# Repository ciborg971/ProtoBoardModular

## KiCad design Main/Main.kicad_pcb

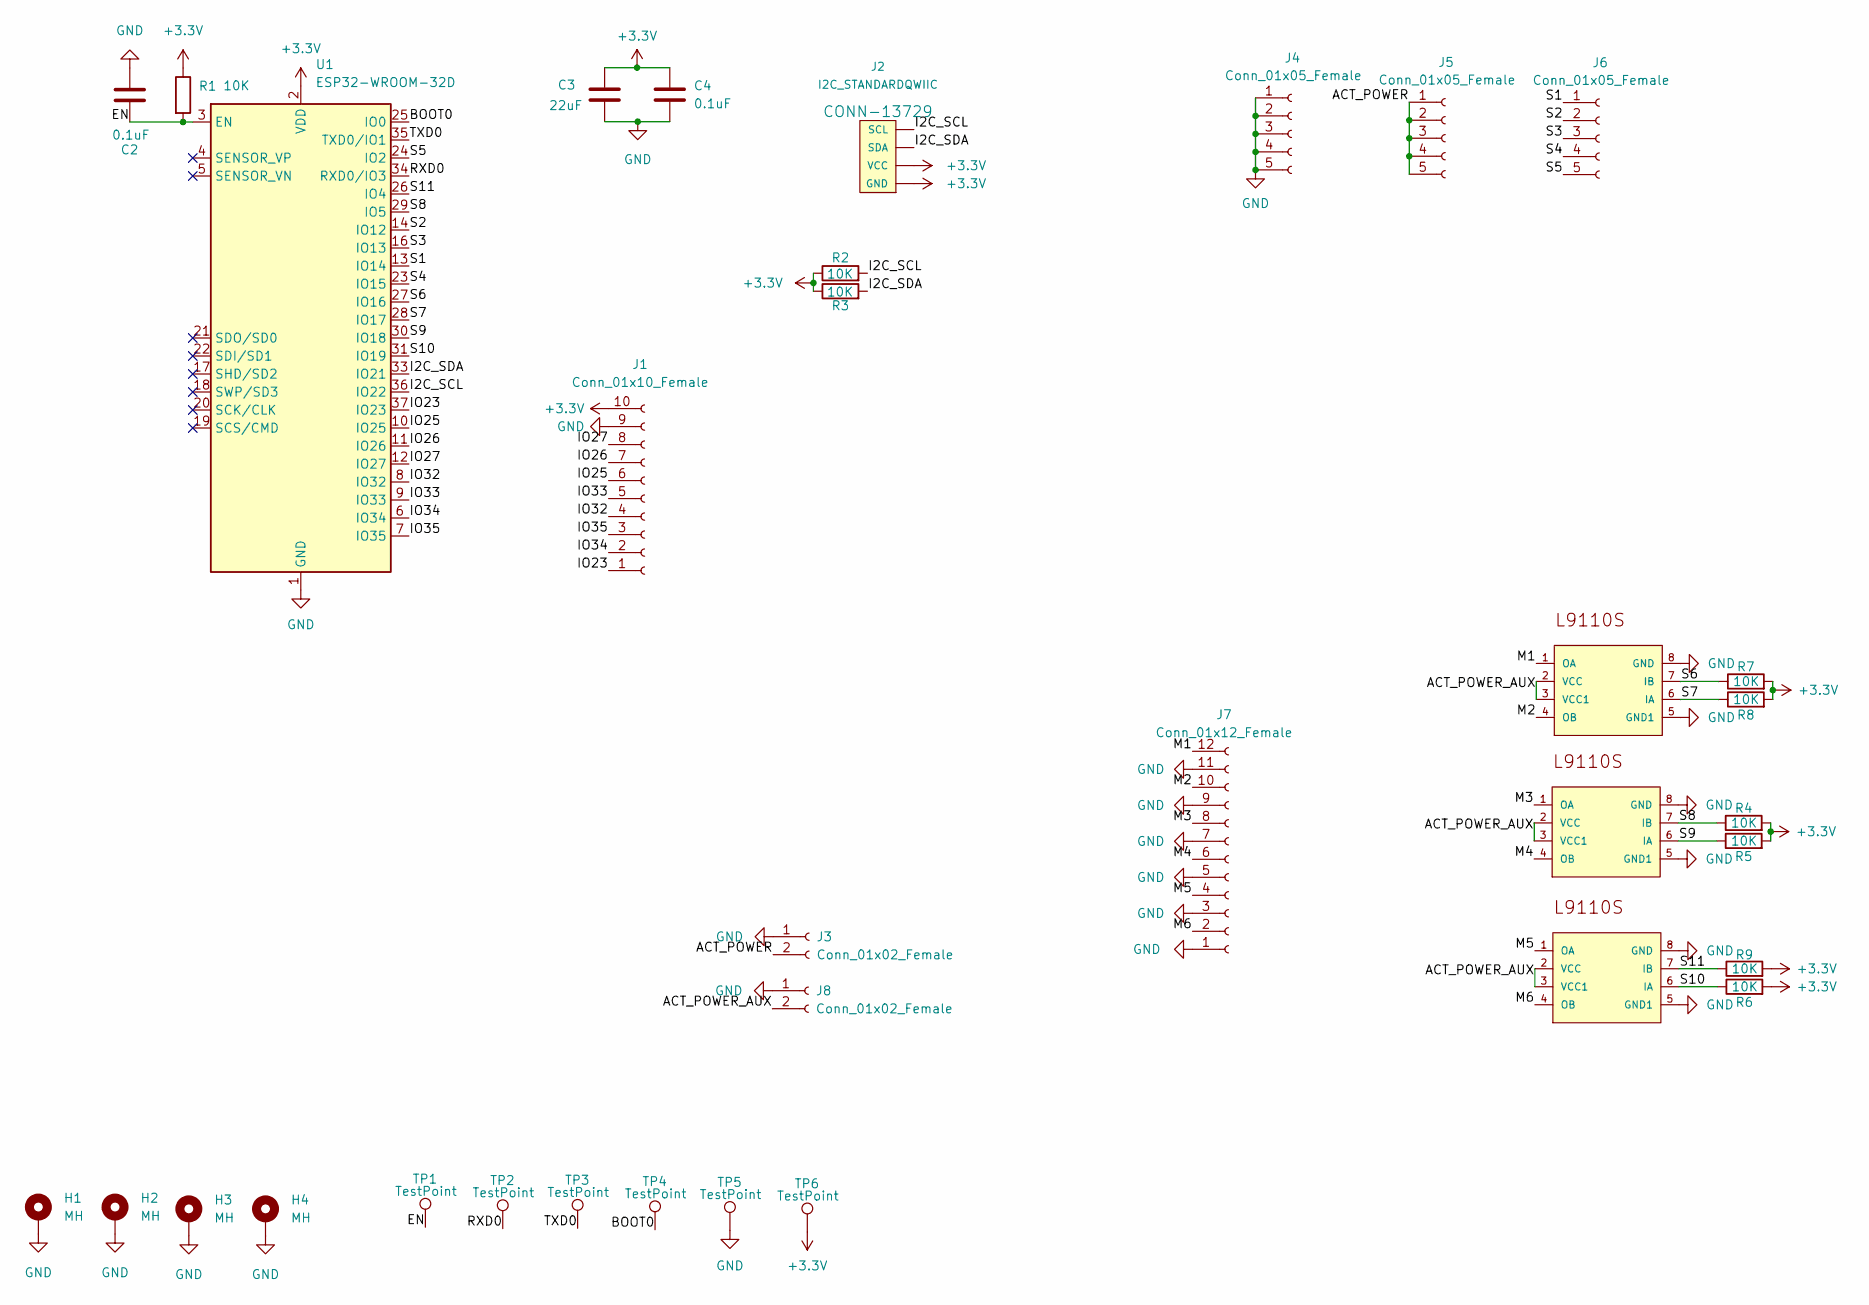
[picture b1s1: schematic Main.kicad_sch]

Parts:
C2, C4: 0.1uF; C_0402_1005Metric; LCSC C178771
C3: 22uF; C_0402_1005Metric; LCSC C2836678
H1, H2, H3, H4: MH; MountingHole_2.2mm_M2_Pad
IC1, IC2, IC3: L9110S; SOIC127P600X150-8; LCSC C2984833
J1: Conn_01x10_Female; Hirose_DF13-10P-1.25DSA_1x10_P1.25mm_Vertical
J2: I2C_STANDARDQWIIC; 1X04_1MM_RA
J3, J8: Conn_01x02_Female; PinSocket_1x02_P2.54mm_Vertical
J4, J5, J6: Conn_01x05_Female; PinHeader_1x05_P2.54mm_Vertical
J7: Conn_01x12_Female; Hirose_DF13-12P-1.25DSA_1x12_P1.25mm_Vertical
R1, R2, R3, R4, R5, R6, R7, R8, R9: 10K; R_0402_1005Metric; LCSC C325396
TP1, TP2, TP3, TP4, TP5, TP6: TestPoint; TestPoint_Pad_1.5x1.5mm
U1: ESP32-WROOM-32D; ESP32-WROOM-32; LCSC C473012

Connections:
+3V3: C3.1, C4.1, J1.10, J2.1 (GND), J2.2 (VCC), R1.1, R2.1, R3.1, R4.2, R5.2, R6.2, R7.2, R8.2, R9.2, TP6.1, U1.2 (VDD)
/ACT_POWER: J3.2, J5.1, J5.2, J5.3, J5.4, J5.5
/ACT_POWER_AUX: IC1.2 (VCC), IC1.3 (VCC1), IC2.2 (VCC), IC2.3 (VCC1), IC3.2 (VCC), IC3.3 (VCC1), J8.2
/BOOT0: TP4.1, U1.25 (IO0)
/EN: C2.2, R1.2, TP1.1, U1.3 (EN)
/I2C_SCL: J2.4 (SCL), R2.2, U1.36 (IO22)
/I2C_SDA: J2.3 (SDA), R3.2, U1.33 (IO21)
/IO23: J1.1, U1.37 (IO23)
/IO25: J1.6, U1.10 (IO25)
/IO26: J1.7, U1.11 (IO26)
/IO27: J1.8, U1.12 (IO27)
/IO32: J1.4, U1.8 (IO32)
/IO33: J1.5, U1.9 (IO33)
/IO34: J1.2, U1.6 (IO34)
/IO35: J1.3, U1.7 (IO35)
/M1: IC3.1 (OA), J7.12
/M2: IC3.4 (OB), J7.10
/M3: IC1.1 (OA), J7.8
/M4: IC1.4 (OB), J7.6
/M5: IC2.1 (OA), J7.4
/M6: IC2.4 (OB), J7.2
/RXD0: TP2.1, U1.34 (RXD0/IO3)
/S1: J6.1, U1.13 (IO14)
/S2: J6.2, U1.14 (IO12)
/S3: J6.3, U1.16 (IO13)
/S4: J6.4, U1.23 (IO15)
/S5: J6.5, U1.24 (IO2)
/S6: IC3.7 (IB), R7.1, U1.27 (IO16)
/S7: IC3.6 (IA), R8.1, U1.28 (IO17)
/S8: IC1.7 (IB), R4.1, U1.29 (IO5)
/S9: IC1.6 (IA), R5.1, U1.30 (IO18)
/S10: IC2.6 (IA), R6.1, U1.31 (IO19)
/S11: IC2.7 (IB), R9.1, U1.26 (IO4)
/TXD0: TP3.1, U1.35 (TXD0/IO1)
GND: C2.1, C3.2, C4.2, H1.1, H2.1, H3.1, H4.1, IC1.5 (GND1), IC1.8 (GND), IC2.5 (GND1), IC2.8 (GND), IC3.5 (GND1), IC3.8 (GND), J1.9, J3.1, J4.1, J4.2, J4.3, J4.4, J4.5, J7.1, J7.3, J7.5, J7.7, J7.9, J7.11, J8.1, TP5.1, U1.1 (GND), U1.15 (GND), U1.38 (GND), U1.39 (GND)

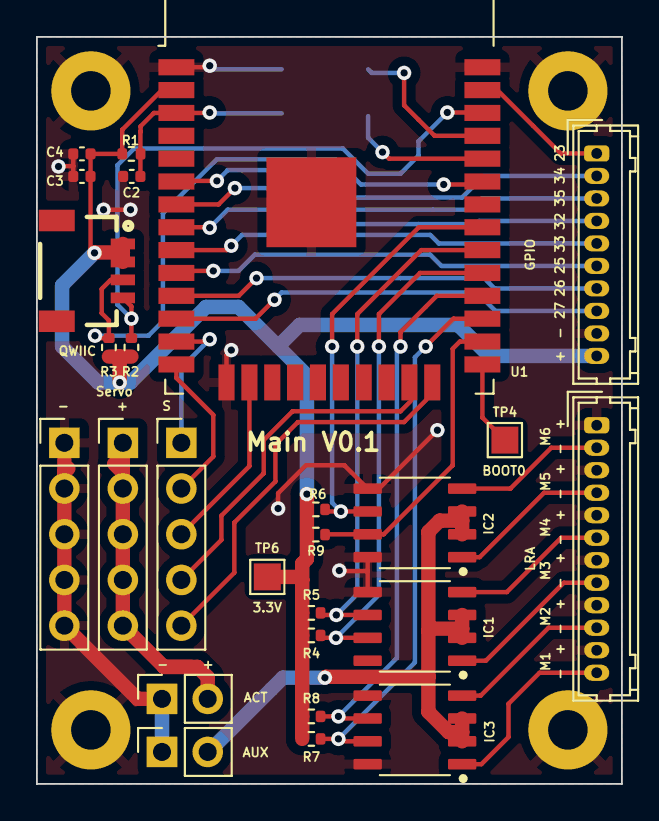
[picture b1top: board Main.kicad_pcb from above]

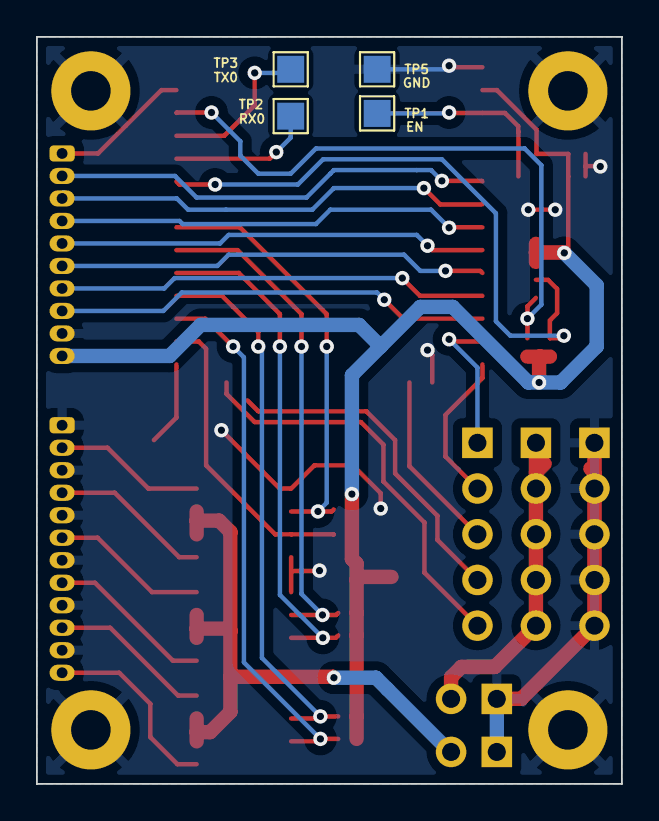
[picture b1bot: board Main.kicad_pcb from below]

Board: 2 copper layers, 32.5 x 41.5 mm, 34 parts (4 on the bottom side), 35 nets.

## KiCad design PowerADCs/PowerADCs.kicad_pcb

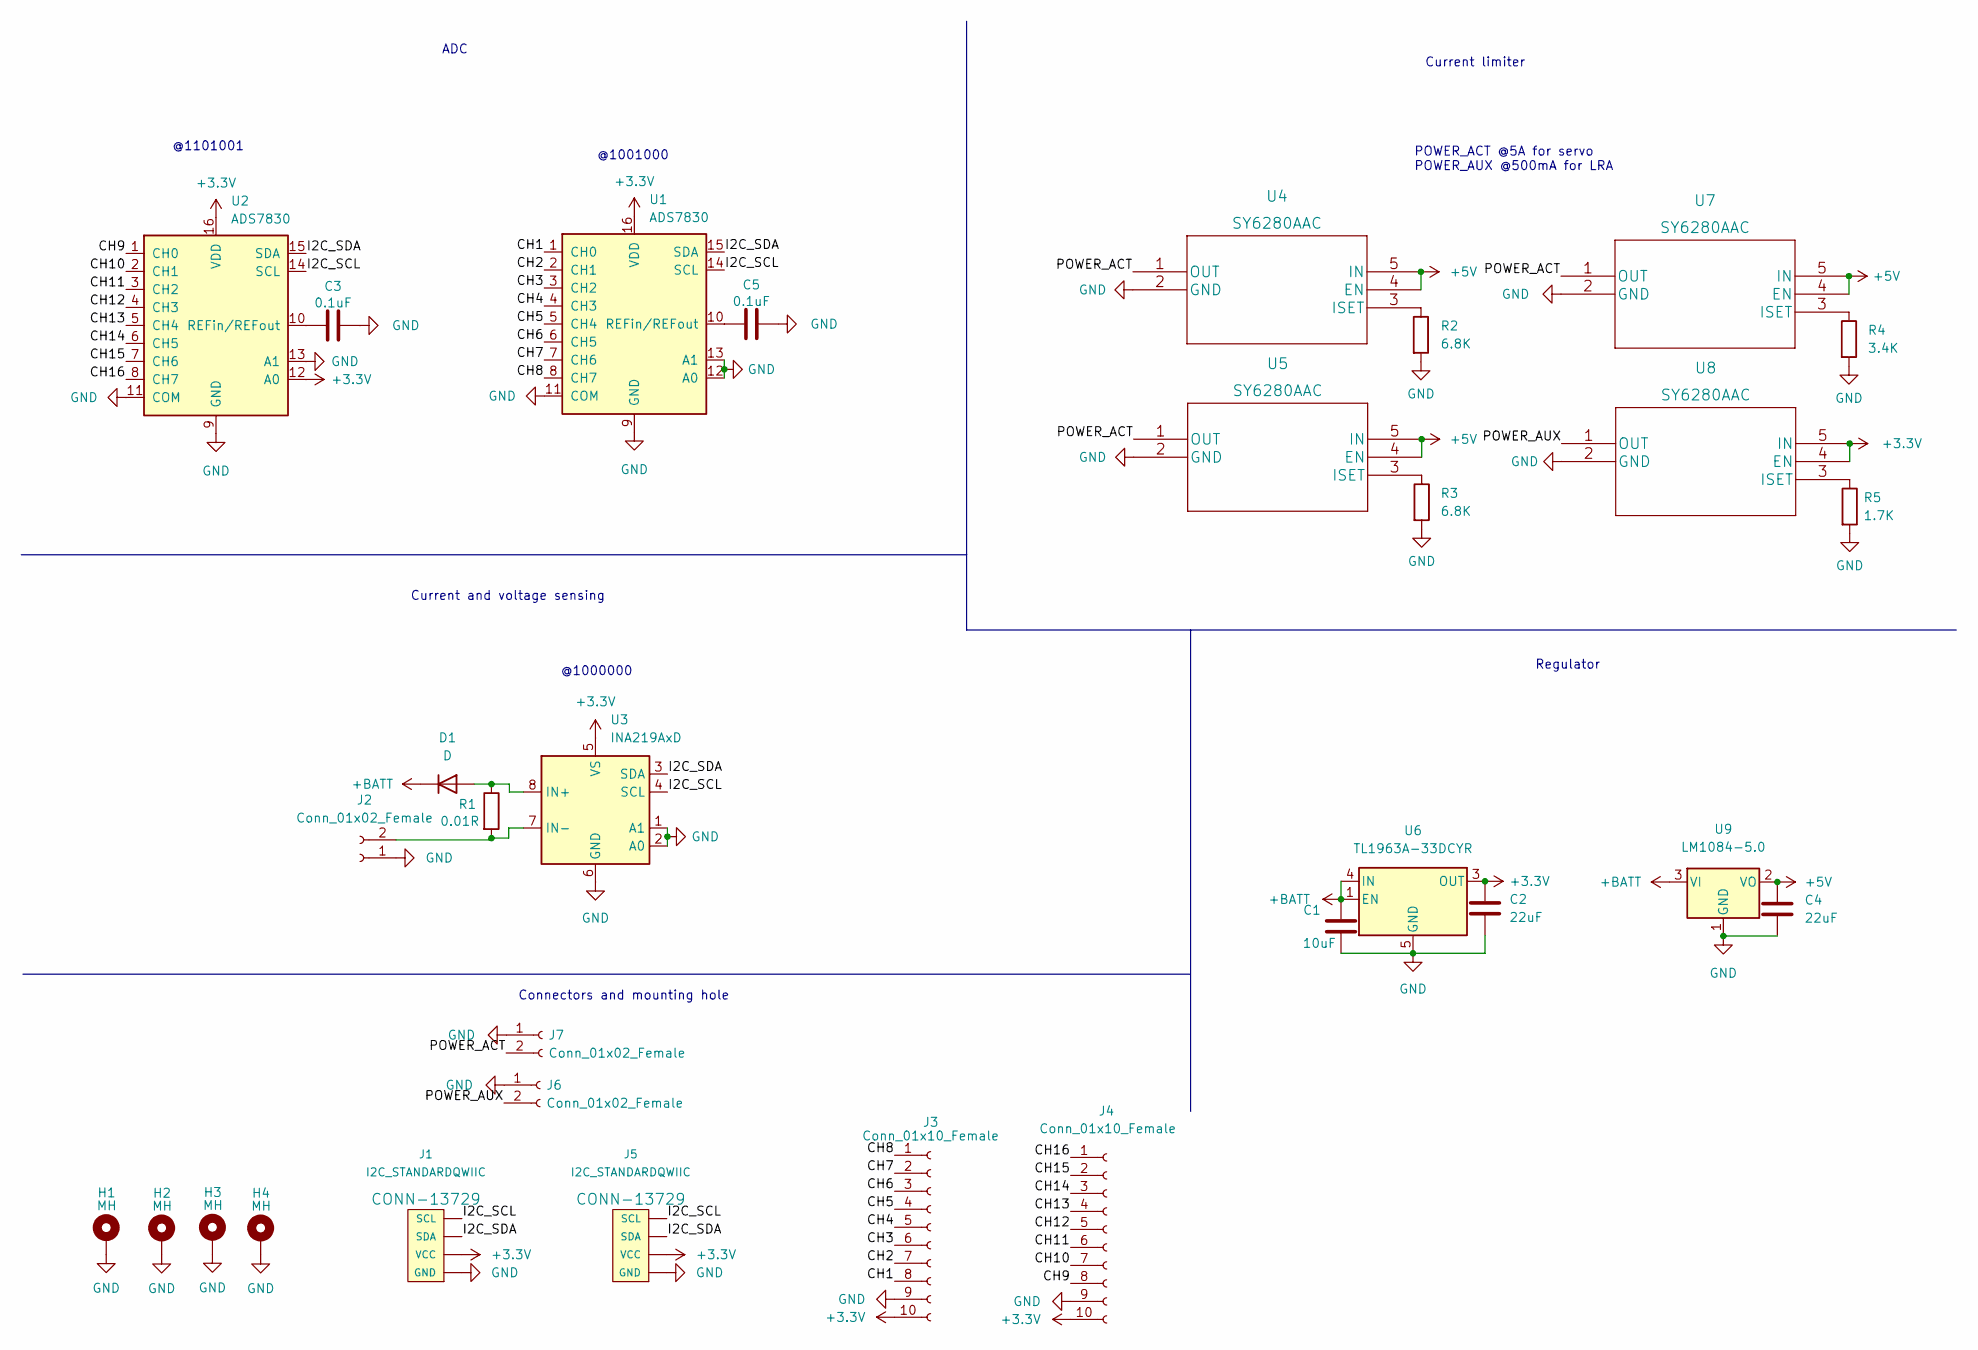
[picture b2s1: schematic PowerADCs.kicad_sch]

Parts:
C1: 10uF; C_0402_1005Metric
C2, C4: 22uF; C_0402_1005Metric
C3, C5: 0.1uF; C_0402_1005Metric
D1: D; D_0402_1005Metric
H1, H2, H3, H4: MH; MountingHole_2.2mm_M2_Pad
J1, J5: I2C_STANDARDQWIIC; 1X04_1MM_RA
J2, J6, J7: Conn_01x02_Female; PinSocket_1x02_P2.54mm_Vertical
J3, J4: Conn_01x10_Female; Hirose_DF13-10P-1.25DSA_1x10_P1.25mm_Vertical
R1: 0.01R; R_0402_1005Metric
R2, R3: 6.8K; R_0402_1005Metric
R4: 3.4K; R_0402_1005Metric
R5: 1.7K; R_0402_1005Metric
U1, U2: ADS7830; TSSOP-16_4.4x5mm_P0.65mm
U3: INA219AxD; SOIC-8_3.9x4.9mm_P1.27mm
U4, U5, U7, U8: SY6280AAC
U6: TL1963A-33DCYR; SOT-223-5
U9: LM1084-5.0; TO-263-2

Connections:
+3V3: C2.1, J1.2 (VCC), J3.10, J4.10, J5.2 (VCC), U1.16 (VDD), U2.12 (A0), U2.16 (VDD), U3.5 (VS), U6.3 (OUT), U8.4 (EN), U8.5 (IN)
+5V: C4.1, U4.4 (EN), U4.5 (IN), U5.4 (EN), U5.5 (IN), U7.4 (EN), U7.5 (IN), U9.2 (VO)
+BATT: C1.1, D1.1 (K), U6.1 (EN), U6.4 (IN), U9.3 (VI)
/CH1: J3.8, U1.1 (CH0)
/CH2: J3.7, U1.2 (CH1)
/CH3: J3.6, U1.3 (CH2)
/CH4: J3.5, U1.4 (CH3)
/CH5: J3.4, U1.5 (CH4)
/CH6: J3.3, U1.6 (CH5)
/CH7: J3.2, U1.7 (CH6)
/CH8: J3.1, U1.8 (CH7)
/CH9: J4.8, U2.1 (CH0)
/CH10: J4.7, U2.2 (CH1)
/CH11: J4.6, U2.3 (CH2)
/CH12: J4.5, U2.4 (CH3)
/CH13: J4.4, U2.5 (CH4)
/CH14: J4.3, U2.6 (CH5)
/CH15: J4.2, U2.7 (CH6)
/CH16: J4.1, U2.8 (CH7)
/I2C_SCL: J1.4 (SCL), J5.4 (SCL), U1.14 (SCL), U2.14 (SCL), U3.4 (SCL)
/I2C_SDA: J1.3 (SDA), J5.3 (SDA), U1.15 (SDA), U2.15 (SDA), U3.3 (SDA)
/POWER_ACT: J7.2, U4.1 (OUT), U5.1 (OUT), U7.1 (OUT)
/POWER_AUX: J6.2, U8.1 (OUT)
GND: C1.2, C2.2, C3.2, C4.2, C5.2, H1.1, H2.1, H3.1, H4.1, J1.1 (GND), J2.1, J3.9, J4.9, J5.1 (GND), J6.1, J7.1, R2.2, R3.2, R4.2, R5.2, U1.9 (GND), U1.12 (A0), U1.13 (A1), U2.9 (GND), U2.13 (A1), U3.1 (A1), U3.2 (A0), U3.6 (GND), U4.2 (GND), U5.2 (GND), U6.5 (GND), U7.2 (GND), U8.2 (GND), U9.1 (GND)
unnamed: C3.1, U2.10 (REFin/REFout)
unnamed: C5.1, U1.10 (REFin/REFout)
unnamed: D1.2 (A), R1.1, U3.8 (IN+)
unnamed: J2.2, R1.2, U3.7 (IN-)
unnamed: R2.1, U4.3 (ISET)
unnamed: R3.1, U5.3 (ISET)
unnamed: R4.1, U7.3 (ISET)
unnamed: R5.1, U8.3 (ISET)

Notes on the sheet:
@1000000
Current and voltage sensing
@1101001
Regulator
Connectors and mounting hole
ADC
POWER_ACT @5A for servo POWER_AUX @500mA for LRA
@1001000
Current limiter

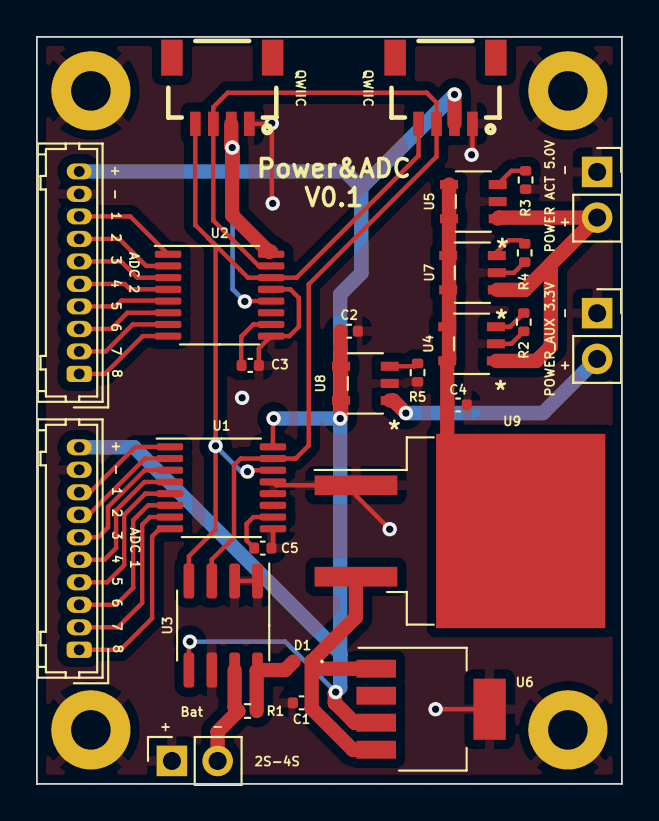
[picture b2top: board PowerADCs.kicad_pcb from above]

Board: 2 copper layers, 32.5 x 41.5 mm, 31 parts (0 on the bottom side), 32 nets.

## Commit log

2022-04-11 Schematic + rooted board
    TODO :
    - capacitor value
2022-04-11 add license
2022-04-12 change ADC's and add seconde qwiic connector
2022-04-12 more silkscreen and fix resistor value for current limiter
2022-04-13 main board : improve silkscreen, LCSC sourcing, capacitor value and JLCPCB files
2022-04-21 PCB cleaning, fix voltage divider values and silkscreen

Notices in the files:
parts and their libraries:
Copyright 2021 Accelerated Designs. All rights reserved.
